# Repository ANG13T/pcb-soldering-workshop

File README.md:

# PCB & Soldering Workshop
Slideshow, KiCad PCB Files, and Assets for the PCB and Soldering Workshop

[Slideshow Link](https://docs.google.com/presentation/d/1vs6tnDx22Qua1xx6uAiyIqPal7wYi3oso5HCmm7cpDM/edit?usp=sharing)

### Part 1: Electronics and Circuits 101
Learn about the underlying science that makes circuits work!

### Part 2: PCB Design with KiCad
Make your own cute and simple cat PCB!

### Part 3: Soldering the Meow Mixer
Develop your soldering skills by assembling the [Meow Mixer](https://retia.io/products/meow-mixer-pcb).

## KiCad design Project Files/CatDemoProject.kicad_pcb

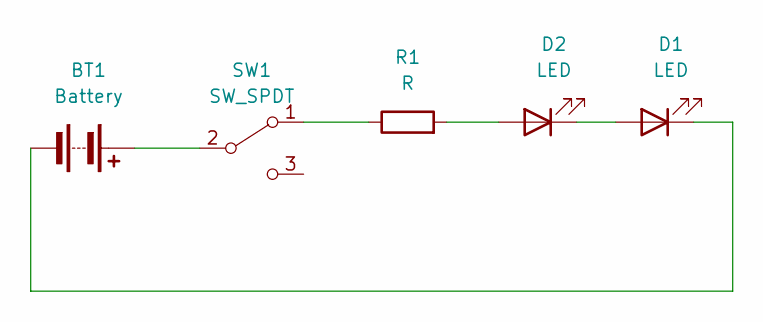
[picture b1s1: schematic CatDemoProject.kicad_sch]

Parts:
BT1: Battery; BatteryHolder_Keystone_1058_1x2032
D1, D2: LED; LED_D3.0mm
R1: R; R_Axial_DIN0207_L6.3mm_D2.5mm_P10.16mm_Horizontal
SW1: SW_SPDT; SW_DIP_SPSTx01_Slide_6.7x4.1mm_W7.62mm_P2.54mm_LowProfile

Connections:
unnamed: BT1.1 (+), SW1.2 (B)
unnamed: BT1.2 (-), D1.1 (K)
unnamed: D1.2 (A), D2.1 (K)
unnamed: D2.2 (A), R1.2
unnamed: R1.1, SW1.1 (A)

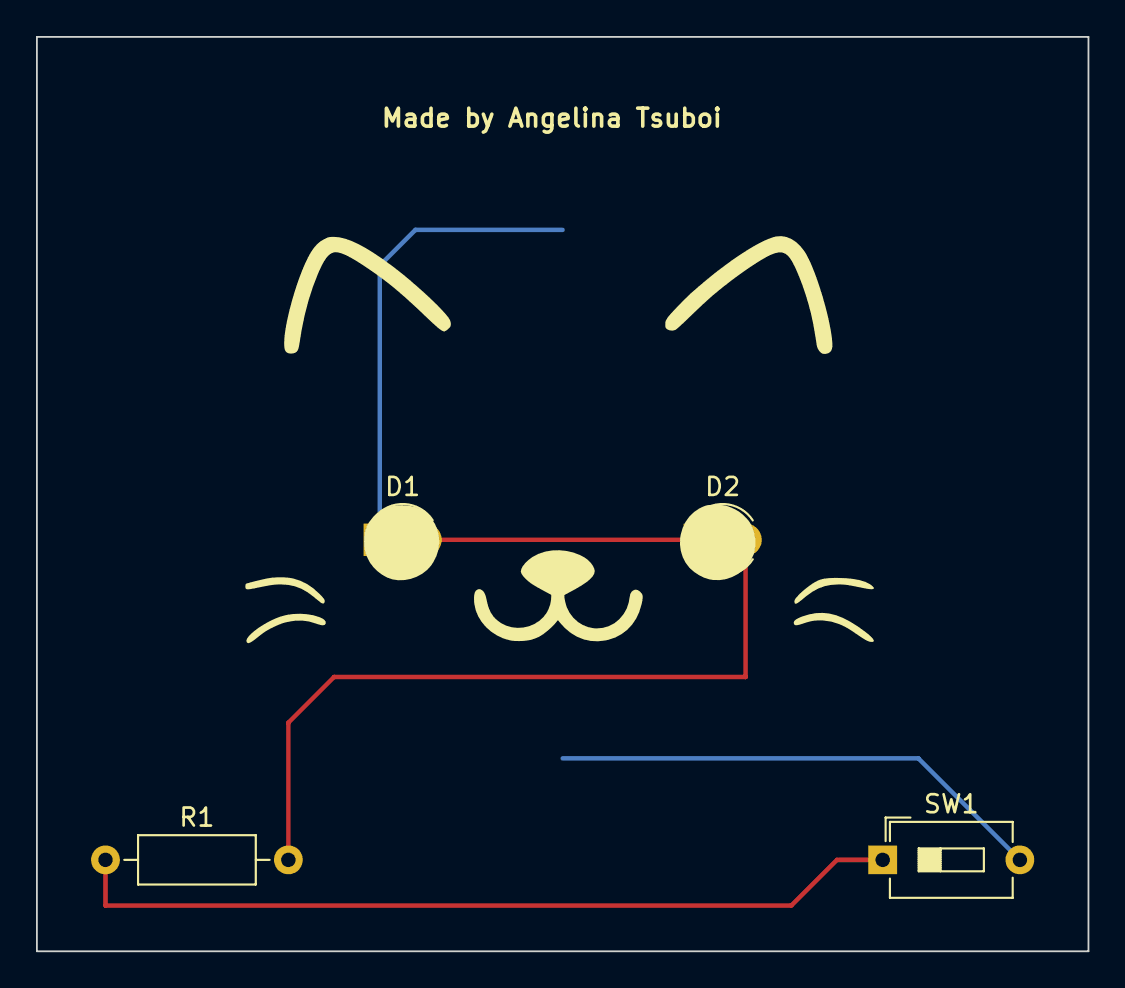
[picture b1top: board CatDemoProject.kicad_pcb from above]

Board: 2 copper layers, 58.4 x 50.8 mm, 5 parts (1 on the bottom side), 5 nets.
